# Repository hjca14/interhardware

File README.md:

# InterBridge Hardware

Hardware do **InterBridge**, uma ponte entre uma linha analógica compatível com
telefone convencional e um aplicativo móvel, por Wi-Fi.

## Escopo deste repositório

Este repositório concentrará o projeto eletrônico no KiCad, as bibliotecas
locais, as decisões de engenharia, as referências e, futuramente, os artefatos
de fabricação (BOM, Gerbers e dados de montagem). O firmware e o aplicativo
móvel não fazem parte deste repositório.

O projeto está em **fase inicial de pesquisa e prototipagem**. Ainda não há um
esquemático ou uma PCB aprovados. Consulte os [requisitos](docs/REQUIREMENTS.md),
a [arquitetura](docs/ARCHITECTURE.md) e as
[decisões registradas](docs/decisions/).

## Arquitetura proposta

- entrada de linha analógica em um conector **RJ11 LINE**;
- saída **RJ11 PHONE** em paralelo/pass-through para preservar o telefone ou
  interfone físico;
- proteção de linha e interface FXO/DAA, preferencialmente baseada no conjunto
  **Si3050 + Si3019**;
- módulo **ESP32-C3** para controle, processamento e conectividade Wi-Fi;
- possibilidade futura de saída por relé para instalações nas quais a abertura
  do portão usa um contato separado.

O pass-through LINE → PHONE deverá ser passivo/fail-safe sempre que a validação
elétrica da instalação permitir, de modo que o aparelho físico continue
funcionando mesmo com o InterBridge sem alimentação.

## Princípios de desenvolvimento

- A seção de telefonia será derivada de um **reference design oficial e
  validado da Skyworks para Si3050 + Si3019**, incluindo as recomendações de BOM
  e layout aplicáveis. Não serão criados valores elétricos, pinagens, footprints
  ou circuitos por suposição.
- Datasheets, reference designs e demais materiais de terceiros serão
  referenciados, e não copiados para o repositório sem que sua licença permita e
  sem necessidade clara.
- Segurança elétrica, isolamento, proteção contra surtos e os requisitos de uma
  futura homologação pela Anatel devem ser considerados desde o início, antes
  da fabricação ou conexão a uma instalação real.
- Arquivos-fonte do KiCad e bibliotecas locais devem ser versionados; saídas de
  fabricação serão geradas de forma reproduzível quando o projeto estiver
  validado.

## Estrutura

```text
kicad/                    fontes do projeto KiCad
docs/                     arquitetura, requisitos e documentação
  decisions/              Architecture Decision Records (ADRs)
  reference-designs/      notas e links para projetos de referência
libraries/
  symbols/                símbolos KiCad mantidos pelo projeto
  footprints/             footprints KiCad mantidos pelo projeto
manufacturing/
  gerbers/                 saídas para fabricação da PCB
  bom/                     listas de materiais
  assembly/                dados e instruções de montagem
```

As pastas inicialmente vazias contêm apenas `.gitkeep`. Nenhum circuito
fictício foi criado para preenchê-las.

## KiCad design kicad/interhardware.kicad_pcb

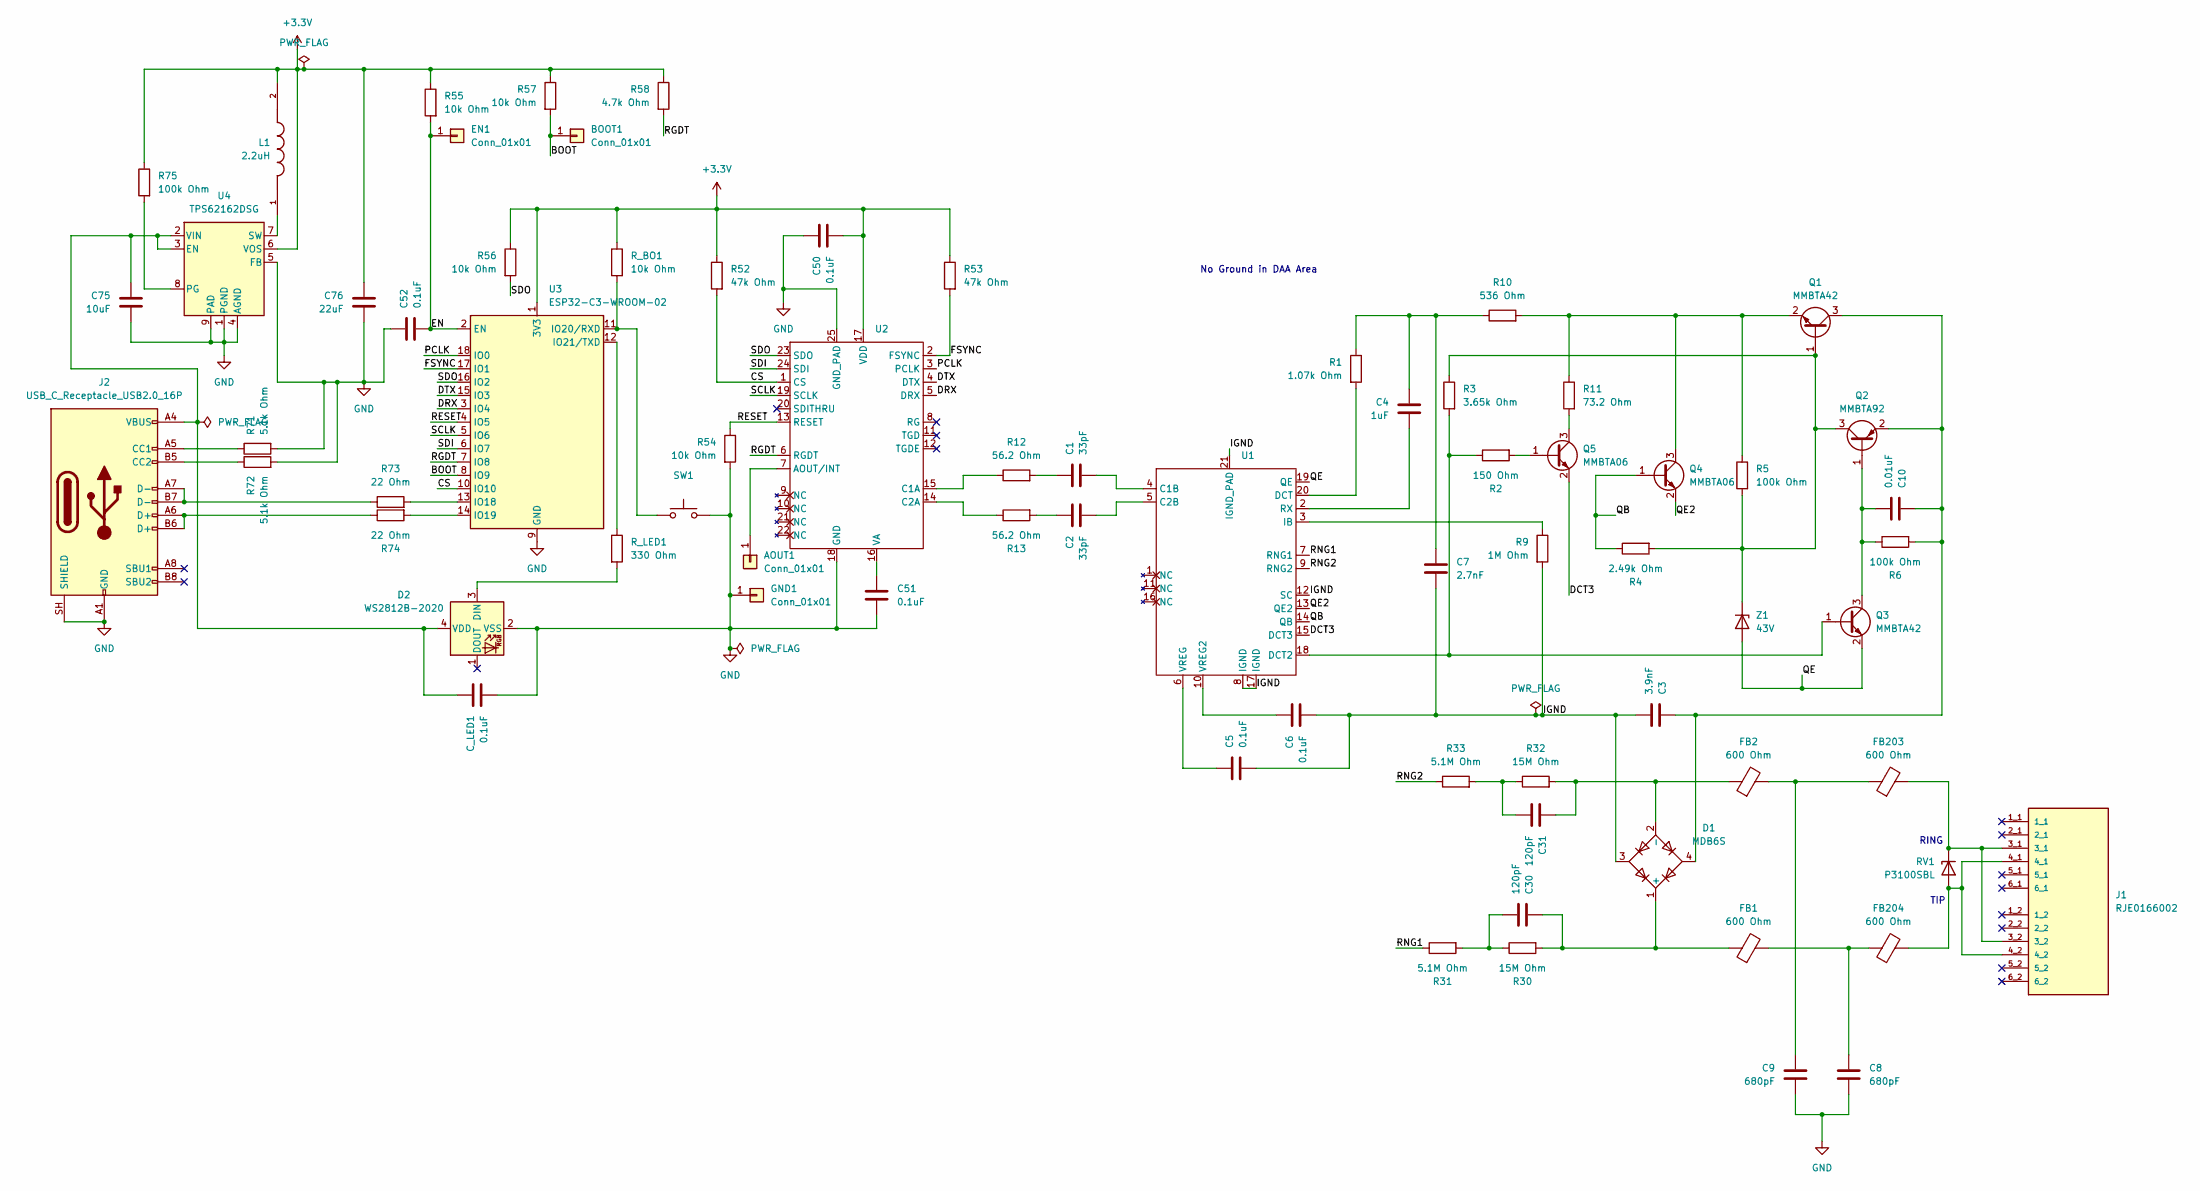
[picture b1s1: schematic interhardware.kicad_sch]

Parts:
AOUT1: Conn_01x01; PinHeader_1x01_P2.54mm_Vertical
BOOT1: Conn_01x01; PinHeader_1x01_P2.54mm_Vertical
C1, C2: 33pF; C_1808_4520Metric; MPN GA342A1XGF330JW31L
C3: 3.9nF; C_1206_3216Metric; MPN GENERIC
C4: 1uF; CP_Elec_4x5.4; MPN EEE-1HA010NR
C5, C6, C50, C51, C52: 0.1uF; C_0603_1608Metric; MPN GENERIC
C7: 2.7nF; C_0603_1608Metric; MPN GENERIC
C8, C9: 680pF; C_1808_4520Metric; MPN GA342QR7GF681KW01L
C10: 0.01uF; C_0603_1608Metric; MPN GENERIC
C30, C31: 120pF; C_1206_3216Metric; MPN GENERIC
C75: 10uF; C_0805_2012Metric; MPN GENERIC
C76: 22uF; C_0805_2012Metric; MPN GENERIC
C_LED1: 0.1uF; C_0603_1608Metric; MPN GENERIC
D1: MDB6S; TSSOP-4_4.4x5mm_P4mm; MPN MDB6S
D2: WS2812B-2020; LED_WS2812B-2020_PLCC4_2.0x2.0mm; MPN WS2812B-2020
EN1: Conn_01x01; PinHeader_1x01_P2.54mm_Vertical
FB1, FB2, FB203, FB204: 600 Ohm; L_0603_1608Metric; MPN BLM18AG601SN1
GND1: Conn_01x01; PinHeader_1x01_P2.54mm_Vertical
J1: RJE0166002; AMPHENOL_RJE0166002; PARTREV A
J2: USB_C_Receptacle_USB2.0_16P; USB_C_Receptacle_GCT_USB4105-xx-A_16P_TopMnt_Horizontal; MPN USB4105-GF-A-060
L1: 2.2uH; IND_VLS3012HBX-2R2M-N; PARTREV N/A
Q1, Q3: MMBTA42; SOT-23; MPN MMBTA42
Q2: MMBTA92; SOT-23; MPN MMBTA92
Q4, Q5: MMBTA06; SOT-23; MPN MMBTA06
R1: 1.07k Ohm; R_1206_3216Metric; MPN GENERIC
R2: 150 Ohm; R_0603_1608Metric; MPN GENERIC
R3: 3.65k Ohm; R_1206_3216Metric; MPN GENERIC
R4: 2.49k Ohm; R_1206_3216Metric; MPN GENERIC
R5, R6, R75: 100k Ohm; R_0603_1608Metric; MPN GENERIC
R9: 1M Ohm; R_0603_1608Metric; MPN GENERIC
R10: 536 Ohm; R_1206_3216Metric; MPN GENERIC
R11: 73.2 Ohm; R_1206_3216Metric; MPN GENERIC
R12, R13: 56.2 Ohm; R_0603_1608Metric; MPN GENERIC
R30, R32: 15M Ohm; R_1206_3216Metric; MPN GENERIC
R31, R33: 5.1M Ohm; R_1206_3216Metric; MPN GENERIC
R52, R53: 47k Ohm; R_0603_1608Metric; MPN GENERIC
R54, R55, R56, R57: 10k Ohm; R_0603_1608Metric; MPN GENERIC
R58: 4.7k Ohm; R_0603_1608Metric; MPN GENERIC
R71, R72: 5.1k Ohm; R_0603_1608Metric; MPN GENERIC
R73, R74: 22 Ohm; R_0603_1608Metric; MPN GENERIC
RV1: P3100SBL; D_SMB; MPN P3100SBL
R_BO1: 10k Ohm; R_0603_1608Metric; MPN GENERIC
R_LED1: 330 Ohm; R_0603_1608Metric; MPN GENERIC
SW1: B3U-1000P; SW_SPST_B3U-1000P; MPN B3U-1000P
U1: 3019-F-FM-QFN40P300X300X90-21N
U2: 3050-E1-FM-QFN50P400X400X80-25N
U3: ESP32-C3-WROOM-02; MPN ESP32-C3-WROOM-02
U4: TPS62162DSG; Texas_DSG0008A_WSON-8-1EP_2x2mm_P0.5mm_EP0.9x1.6mm_ThermalV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; MPN TPS62162DSG
Z1: 43V; D_SOD-123; MPN MMSZ43T1G

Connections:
+3.3V: C50.2, C76.1, L1.2, R52.1, R53.1, R55.1, R56.1, R57.1, R58.1, R75.1, R_BO1.1, U2.17 (VDD), U3.1 (3V3), U4.6 (VOS)
/BOOT: BOOT1.1 (Pin_1_1), R57.2, U3.8 (IO9)
/CS: R52.2, U2.1 (CS), U3.10 (IO10)
/DCT3: Q5.2 (E), U1.15 (DCT3)
/DRX: U2.5 (DRX), U3.3 (IO4)
/DTX: U2.4 (DTX), U3.15 (IO3)
/EN: C52.2, EN1.1 (Pin_1_1), R55.2, U3.2 (EN)
/FSYNC: R53.2, U2.2 (FSYNC), U3.17 (IO1)
/IGND: C3.2, C5.2, C6.2, C7.2, D1.3, R9.2, U1.8 (IGND), U1.12 (SC), U1.17 (IGND), U1.21 (IGND_PAD)
/PCLK: U2.3 (PCLK), U3.18 (IO0)
/QB: Q4.1 (B), R4.1, U1.14 (QB)
/QE: Q3.2 (E), U1.19 (QE), Z1.2 (A)
/QE2: Q4.2 (E), U1.13 (QE2)
/RESET: R54.1, U2.13 (RESET), U3.4 (IO5)
/RGDT: R58.2, U2.6 (RGDT), U3.7 (IO8)
/RNG1: R31.1, U1.7 (RNG1)
/RNG2: R33.1, U1.9 (RNG2)
/SCLK: U2.19 (SCLK), U3.5 (IO6)
/SDI: U2.24 (SDI), U3.6 (IO7)
/SDO: R56.2, U2.23 (SDO), U3.16 (IO2)
GND: C8.2, C9.2, C50.1, C51.2, C52.1, C75.2, C76.2, C_LED1.2, D2.2 (VSS), GND1.1 (Pin_1_1), J2.A1 (GND), J2.A12 (GND), J2.B1 (GND), J2.B12 (GND), J2.SH (SHIELD), R54.2, R71.2, R72.2, SW1.2, U2.18 (GND), U2.25 (GND_PAD), U3.9 (GND), U3.19 (GND), U4.1 (PGND), U4.4 (AGND), U4.5 (FB), U4.9 (PAD)
unnamed: AOUT1.1 (Pin_1_1), U2.7 (AOUT/INT)
unnamed: C1.1, R12.2
unnamed: C2.1, R13.2
unnamed: C4.1, C7.1, R1.1, R10.1
unnamed: C8.1, FB1.2, FB204.1
unnamed: C9.1, FB2.2, FB203.1
unnamed: C30.2, R30.1, R31.2
unnamed: C31.2, R32.1, R33.2
unnamed: C30.1, D1.1 (+), FB1.1, R30.2
unnamed: C31.1, D1.2 (-), FB2.1, R32.2
unnamed: D2.3 (DIN), R_LED1.2
unnamed: C75.1, C_LED1.1, D2.4 (VDD), J2.A4 (VBUS), J2.A9 (VBUS), J2.B4 (VBUS), J2.B9 (VBUS), U4.2 (VIN), U4.3 (EN)
unnamed: J2.A5 (CC1), R71.1
unnamed: J2.B5 (CC2), R72.1
unnamed: J2.A6 (D+), J2.B6 (D+), R74.1
unnamed: J2.A7 (D-), J2.B7 (D-), R73.1
unnamed: Q1.1 (B), Q2.3 (C), R3.1, R4.2, R5.2, Z1.1 (K)
unnamed: C3.1, C10.1, D1.4, Q1.3 (C), Q2.2 (E), R6.2
unnamed: Q1.2 (E), Q4.3 (C), R5.1, R10.2, R11.1
unnamed: C10.2, Q2.1 (B), Q3.3 (C), R6.1
unnamed: Q3.1 (B), R2.1, R3.2, U1.18 (DCT2)
unnamed: Q5.1 (B), R2.2
unnamed: Q5.3 (C), R11.2
unnamed: FB204.2, J1.4_1, J1.4_2, RV1.2 (A)
unnamed: FB203.2, J1.3_1, J1.3_2, RV1.1 (K)
unnamed: C1.2, U1.4 (C1B)
unnamed: C2.2, U1.5 (C2B)
unnamed: R1.2, U1.20 (DCT)
unnamed: R9.1, U1.3 (IB)
unnamed: C4.2, U1.2 (RX)
unnamed: C6.1, U1.10 (VREG2)
unnamed: C5.1, U1.6 (VREG)
unnamed: R12.1, U2.15 (C1A)
unnamed: R13.1, U2.14 (C2A)
unnamed: C51.1, U2.16 (VA)
unnamed: R73.2, U3.13 (IO18)
unnamed: R74.2, U3.14 (IO19)
unnamed: R_BO1.2, SW1.1, U3.11 (IO20/RXD)
unnamed: R_LED1.1, U3.12 (IO21/TXD)
unnamed: R75.2, U4.8 (PG)
unnamed: L1.1, U4.7 (SW)

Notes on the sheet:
RING
No Ground in DAA Area
TIP

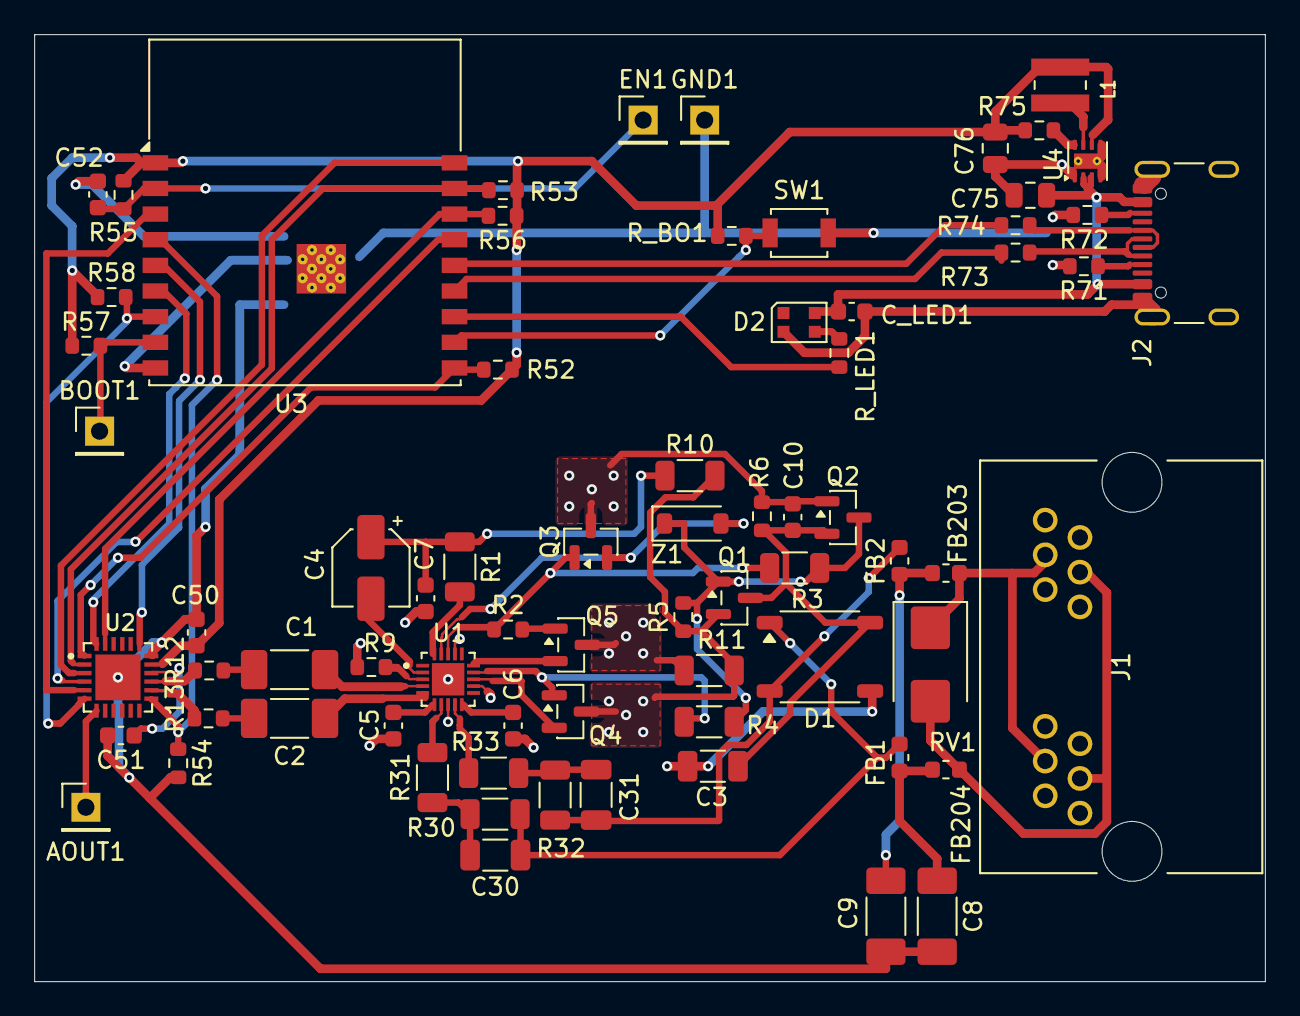
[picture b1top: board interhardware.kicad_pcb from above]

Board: 2 copper layers, 72.0 x 55.4 mm, 72 parts (0 on the bottom side), 62 nets.

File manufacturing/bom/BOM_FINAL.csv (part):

Refs,Qty,Value,Manufacturer,MPN,Description,Tolerance,Power_Rating,Voltage_Rating,Dielectric_or_Type,Package,Footprint,DNP,Procurement_Class,Notes
"C1,C2",2,33pF,Murata,GA342A1XGF330JW31L,Safety isolation capacitor,±5%,N/A,250VAC,X1/Y2 safety ceramic,1808,Capacitor_SMD:C_1808_4520Metric,No,LOCKED,Isolation barrier; exact safety-certified MPN.
C4,1,1uF,Panasonic,EEE-1HA010NR,Aluminum electrolytic capacitor,±20%,N/A,50V,Aluminum electrolytic,4x5.4mm SMD,Capacitor_SMD:CP_Elec_4x5.4,No,LOCKED,
"C8,C9",2,680pF,Murata,GA342QR7GF681KW01L,Safety isolation capacitor,±10%,N/A,250VAC,X1/Y2 safety ceramic,1808,Capacitor_SMD:C_1808_4520Metric,No,LOCKED,Isolation barrier; exact safety-certified MPN.
D2,1,WS2812B-2020,Worldsemi,WS2812B-2020,Addressable RGB LED,N/A,N/A,5V nominal,Integrated LED/controller,PLCC-4 2.0x2.0mm,LED_SMD:LED_WS2812B-2020_PLCC4_2.0x2.0mm,No,LOCKED,
"FB1,FB2,FB203,FB204",4,600 Ohm,Murata,BLM18AG601SN1,"Ferrite bead, 600 ohm at 100MHz",±25% impedance,N/A,50VDC,"Ferrite bead, >=200mA",0603,Inductor_SMD:L_0603_1608Metric,No,LOCKED,
J1,1,RJE0166002,Amphenol Communications Solutions,RJE0166002,Dual 6P6C right-angle jack,N/A,N/A,N/A,THT connector,Dual 6P6C right-angle THT,interbridge_telephony:AMPHENOL_RJE0166002,No,LOCKED,"One physical part; _1 LINE, _2 PHONE; contacts 3 RING / 4 TIP."
J2,1,USB4105-GF-A-060,GCT,USB4105-GF-A-060,USB Type-C USB2 receptacle,N/A,N/A,5V,16-contact horizontal top-mount,USB-C,Connector_USB:USB_C_Receptacle_GCT_USB4105-xx-A_16P_TopMnt_Horizontal,No,LOCKED,Current designator is J2 (earlier documentation called it J4).
L1,1,2.2uH,TDK,VLS3012HBX-2R2M-N,Shielded power inductor,±20%,Isat >=2.84A,N/A,"Wirewound shielded, DCR <=106mOhm",VLS3012,interbridge_telephony:IND_VLS3012HBX-2R2M-N,No,LOCKED,
RV1,1,P3100SBL,Littelfuse,P3100SBL,Bidirectional SIDACtor,N/A,N/A,275V standoff,"SIDACtor, not TVS",DO-214AA / SMB,Diode_SMD:D_SMB,No,LOCKED,
SW1,1,B3U-1000P,Omron,B3U-1000P,Normally-open tactile switch,N/A,N/A,N/A,Momentary SPST-NO,SMD,Button_Switch_SMD:SW_SPST_B3U-1000P,No,LOCKED,
U1,1,SI3019-F-FM,Skyworks Solutions,SI3019-F-FM,Line-side DAA IC,N/A,N/A,Per datasheet,QFN-20 + exposed IGND,QFN-20-1EP,interbridge_telephony:3019-F-FM-QFN40P300X300X90-21N,No,LOCKED,Exposed electrical pad 21 maps to IGND.
U2,1,SI3050-E1-FM,Skyworks Solutions,SI3050-E1-FM,System-side DAA IC,N/A,N/A,Per datasheet,QFN-24 + exposed GND,QFN-24-1EP,interbridge_telephony:3050-E1-FM-QFN50P400X400X80-25N,No,LOCKED,Exposed electrical pad 25 maps to GND.
U3,1,ESP32-C3-WROOM-02,Espressif Systems,ESP32-C3-WROOM-02,Wi-Fi/BLE module with PCB antenna,N/A,N/A,3.0-3.6V,Integrated PCB antenna (not -02U),Module,RF_Module:ESP32-C3-WROOM-02,No,LOCKED,
U4,1,TPS62162DSG,Texas Instruments,TPS62162DSG,3.3V 1A step-down converter,N/A,N/A,3-17V input,WSON-8 + exposed pad,WSON-8-1EP DSG,Package_SON:Texas_DSG0008A_WSON-8-1EP_2x2mm_P0.5mm_EP0.9x1.6mm_ThermalVias,No,LOCKED,
Z1,1,43V,onsemi,MMSZ43T1G,43V Zener diode,±5%,500mW,43V nominal,Zener,SOD-123,Diode_SMD:D_SOD-123,No,LOCKED,
D1,1,MDB6S,onsemi,MDB6S,"1 A, 600 V single-phase bridge rectifier",N/A,N/A,600 V repetitive peak reverse,"Single-phase bridge rectifier, 1 A",TSSOP-4 / MDBxS,Package_SO:TSSOP-4_4.4x5mm_P4mm,No,LOCKED,Meets/exceeds the reference-design requirement of 0.8 A / 400 V.
C3,1,3.9nF,GENERIC,GENERIC,DAA high-voltage capacitor,±20%,N/A,>=250VDC,X7R ceramic,1206,Capacitor_SMD:C_1206_3216Metric,No,EQUIVALENT_ALLOWED,"EVB specifies 250V, 20%, X7R; PCB package is larger than EVB 0805."
"C30,C31",2,120pF,GENERIC,GENERIC,DAA high-voltage capacitor,±10%,N/A,>=250VDC,X7R ceramic,1206,Capacitor_SMD:C_1206_3216Metric,No,EQUIVALENT_ALLOWED,"EVB specifies 250V, 10%, X7R; PCB package is larger than EVB 0805."
"C5,C6,C50,C51",4,0.1uF,GENERIC,GENERIC,DAA bypass capacitor,±20%,N/A,>=16VDC,X7R ceramic,0603,Capacitor_SMD:C_0603_1608Metric,No,EQUIVALENT_ALLOWED,EVB BOM: 16V X7R 20%.
C7,1,2.7nF,GENERIC,GENERIC,DAA capacitor,±20%,N/A,>=50VDC,X7R ceramic,0603,Capacitor_SMD:C_0603_1608Metric,No,EQUIVALENT_ALLOWED,EVB BOM: 50V X7R 20%.
C10,1,0.01uF,GENERIC,GENERIC,DAA capacitor,±20%,N/A,>=16VDC,X7R ceramic,0603,Capacitor_SMD:C_0603_1608Metric,No,EQUIVALENT_ALLOWED,"EVB BOM specifies X7R, 20%; 16V minimum sourcing constraint for low-voltage DAA rail."
C52,1,0.1uF,GENERIC,GENERIC,Digital decoupling capacitor,±10%,N/A,>=10VDC,X7R ceramic,0603,Capacitor_SMD:C_0603_1608Metric,No,EQUIVALENT_ALLOWED,"Digital-domain decoupling, not an EVB line-side capacitor."
C_LED1,1,0.1uF,GENERIC,GENERIC,LED local decoupling capacitor,±10%,N/A,>=10VDC,X7R ceramic,0603,Capacitor_SMD:C_0603_1608Metric,No,EQUIVALENT_ALLOWED,
C75,1,10uF,GENERIC,GENERIC,TPS62162 input capacitor,±20%,N/A,>=25VDC,X7R or X5R ceramic,0805,Capacitor_SMD:C_0805_2012Metric,No,EQUIVALENT_ALLOWED,Voltage rating covers TPS62162 17V maximum input; account for DC-bias derating.
C76,1,22uF,GENERIC,GENERIC,TPS62162 output capacitor,±20%,N/A,>=6.3VDC,X7R or X5R ceramic,0805,Capacitor_SMD:C_0805_2012Metric,No,EQUIVALENT_ALLOWED,3.3V output; account for DC-bias derating.
"Q1,Q3",2,MMBTA42,GENERIC,MMBTA42,High-voltage NPN transistor,N/A,SOT-23 dissipation; verify assembly thermal limits,VCEO >=300V,"NPN, IC >=500mA",SOT-23,Package_TO_SOT_SMD:SOT-23,No,EQUIVALENT_ALLOWED,Reference design uses MMBTA42 family; no manufacturer frozen.
Q2,1,MMBTA92,GENERIC,MMBTA92,High-voltage PNP transistor,N/A,SOT-23 dissipation; verify assembly thermal limits,VCEO >=300V,"PNP, IC >=500mA",SOT-23,Package_TO_SOT_SMD:SOT-23,No,EQUIVALENT_ALLOWED,Reference design uses MMBTA92 family; no manufacturer frozen.
"Q4,Q5",2,MMBTA06,GENERIC,MMBTA06,NPN transistor,N/A,SOT-23 dissipation; verify assembly thermal limits,VCEO >=80V,"NPN, IC >=500mA",SOT-23,Package_TO_SOT_SMD:SOT-23,No,EQUIVALENT_ALLOWED,Reference design uses MMBTA06 family; no manufacturer frozen.
R1,1,1.07k Ohm,GENERIC,GENERIC,Thick-film resistor,±1%,>=0.5W,>=200V,Thick-film,1206,Resistor_SMD:R_1206_3216Metric,No,EQUIVALENT_ALLOWED,DAA EVB requires 1/2W.
R2,1,150 Ohm,GENERIC,GENERIC,Thick-film resistor,±1%,>=0.0625W,>=25V,Thick-film,0603,Resistor_SMD:R_0603_1608Metric,No,EQUIVALENT_ALLOWED,DAA EVB requires 1/16W.
R3,1,3.65k Ohm,GENERIC,GENERIC,Thick-film resistor,±1%,>=0.5W,>=200V,Thick-film,1206,Resistor_SMD:R_1206_3216Metric,No,EQUIVALENT_ALLOWED,DAA EVB requires 1/2W.
R4,1,2.49k Ohm,GENERIC,GENERIC,Thick-film resistor,±1%,>=0.5W,>=200V,Thick-film,1206,Resistor_SMD:R_1206_3216Metric,No,EQUIVALENT_ALLOWED,DAA EVB requires 1/2W.
"R5,R6",2,100k Ohm,GENERIC,GENERIC,Thick-film resistor,±5%,>=0.0625W,>=25V,Thick-film,0603,Resistor_SMD:R_0603_1608Metric,No,EQUIVALENT_ALLOWED,DAA EVB requires 1/16W.
R9,1,1M Ohm,GENERIC,GENERIC,Thick-film resistor,±5%,>=0.1W,>=50V,Thick-film,0603,Resistor_SMD:R_0603_1608Metric,No,EQUIVALENT_ALLOWED,DAA bias resistor.
R10,1,536 Ohm,GENERIC,GENERIC,Thick-film resistor,±1%,>=0.25W,>=200V,Thick-film,1206,Resistor_SMD:R_1206_3216Metric,No,EQUIVALENT_ALLOWED,DAA EVB requires 1/4W.
R11,1,73.2 Ohm,GENERIC,GENERIC,Thick-film resistor,±1%,>=0.5W,>=200V,Thick-film,1206,Resistor_SMD:R_1206_3216Metric,No,EQUIVALENT_ALLOWED,DAA EVB requires 1/2W.
"R12,R13",2,56.2 Ohm,GENERIC,GENERIC,Thick-film resistor,±1%,>=0.0625W,>=25V,Thick-film,0603,Resistor_SMD:R_0603_1608Metric,No,EQUIVALENT_ALLOWED,DAA EVB requires 1/16W.
"R30,R32",2,15M Ohm,GENERIC,GENERIC,Thick-film resistor,±5%,>=0.125W,>=200V,Thick-film,1206,Resistor_SMD:R_1206_3216Metric,No,EQUIVALENT_ALLOWED,High-value DAA line-side resistor; EVB requires 1/8W.
"R31,R33",2,5.1M Ohm,GENERIC,GENERIC,Thick-film resistor,±5%,>=0.125W,>=200V,Thick-film,1206,Resistor_SMD:R_1206_3216Metric,No,EQUIVALENT_ALLOWED,High-value DAA line-side resistor; EVB requires 1/8W.
"R52,R53,R54",3,47k Ohm,GENERIC,GENERIC,Thick-film resistor,±5%,>=0.0625W,>=25V,Thick-film,0603,Resistor_SMD:R_0603_1608Metric,No,EQUIVALENT_ALLOWED,DAA/digital control resistor.
"R55,R_BO1",2,10k Ohm,GENERIC,GENERIC,Thick-film resistor,±1%,>=0.1W,>=25V,Thick-film,0603,Resistor_SMD:R_0603_1608Metric,No,EQUIVALENT_ALLOWED,Digital pull-up/pull-down.
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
